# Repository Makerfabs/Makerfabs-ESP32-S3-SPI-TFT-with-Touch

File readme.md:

# Makerfabs ESP32-S3 SPI TFT with Touch

```c++
/*
Version:		V1.4
Author:			Vincent
Create Date:	2022/7/13
Note:
			2022/12/29	V1.4: Change wiki link
			2022/10/10	V1.3: Add Touch Keyboard demo and Back Light demo.
			2022/8/19	V1.2: Add hardware file.
			2022/8/18	V1.1: Add two demo.
			
*/
```

[toc]

# Makerfabs

[Makerfabs home page](https://www.makerfabs.com/)

[Makerfabs Wiki](https://wiki.makerfabs.com/)

# Makerfabs ESP32-S3 SPI TFT with Touch
## Intruduce

Product Link ：[ESP32-S3 SPI TFT with Touch 3.5'' ILI9488](https://www.makerfabs.com/esp32-s3-spi-tft-with-touch-ili9488.html)

Wiki Link : [ESP32-S3 SPI 3.5" TFT with Touch](https://wiki.makerfabs.com/ESP32_S3_SPI_3.5_TFT_with_Touch.html)

The 3.5" 320x480 TFT LCD driver is ILI9488, it uses SPI line for communication with ESP32-S3. You can freely use some of GPIO, to connect the ESP32-S3 display with sensors/ actuators, suitable for IoT applications.

## Feature

- Wi-Fi (2.4 GHz band)
- Bluetooth Low Energy
- Dual high performance Xtensa® 32-bit LX7 CPU cores
- Ultra Low Power co-processor running either RISC-V or FSM core
- Multiple peripherals
- Built-in security hardware
- USB OTG interface
- USB Serial/JTAG Controller
- Arduino Compatible: You can play it with Arduino IDE
- LCD 3.5 inch Amorphous-TFT-LCD (Thin Film Transistor Liquid Crystal Display) for mobile-phone or handy electrical equipment
- LCD Driver: ILI9488(SPI)
- LCD Resolution: 320*480
- FT6236 Series ICs are single-chip capacitive touch panel controller IC with a built-in 16 bit enhanced Micro-controller unit (MCU)
- Power supply: 5V, Type-C USB
- Micro SD card slot on the board
- Dual USB Type-C: one for native USB and one for USB-to-UART
- Board size: 66mm * 85mm

# Code Explain

## Complier Option

- Install board : ESP32 .
- Install library : LovyanGFX library. 
- Use type-c use cable connect USB-TTL to PC.
- Upload codes, select "ESP32-S3 DEV Module" and "UART0"

## Firmware

### S3_9488

A simple test procedure. Touch the black area in the middle of the screen, and the screen starts showing solid colors in turn. Finally, an SD card image is displayed.

## Example

### image_display.ino

The BMP image of the SD card is displayed.

### indoor

[ESP32 Touch_Indoor Environment Expansion](https://www.makerfabs.com/esp32-touch-indoor-environment-expansion.html)

Test air temperature, humidity, and TVOC values with extension plate.

### Touch Keyboard

Added an inherited three custom keyboard keyboard Demo, including text input + key combination, numeric keypad, arrow keys + space.

### Back Light

Periodically adjust the brightness of the backlight

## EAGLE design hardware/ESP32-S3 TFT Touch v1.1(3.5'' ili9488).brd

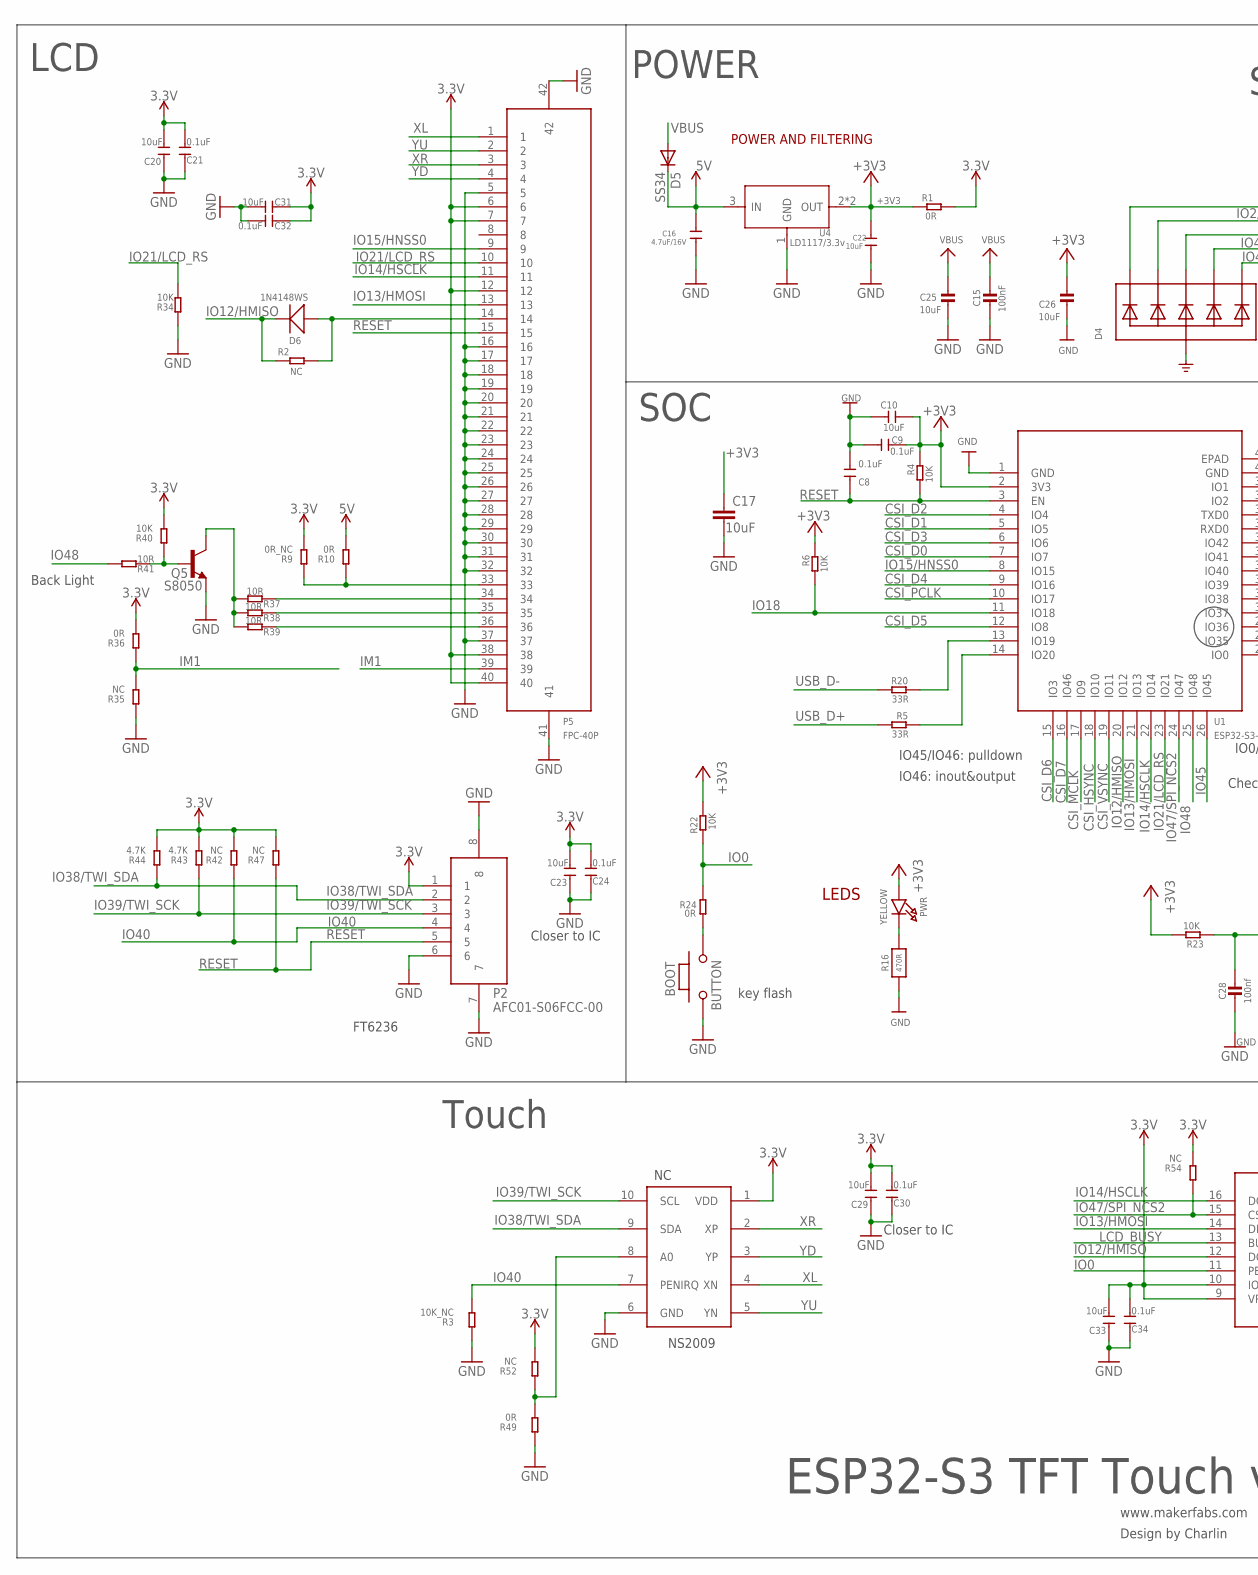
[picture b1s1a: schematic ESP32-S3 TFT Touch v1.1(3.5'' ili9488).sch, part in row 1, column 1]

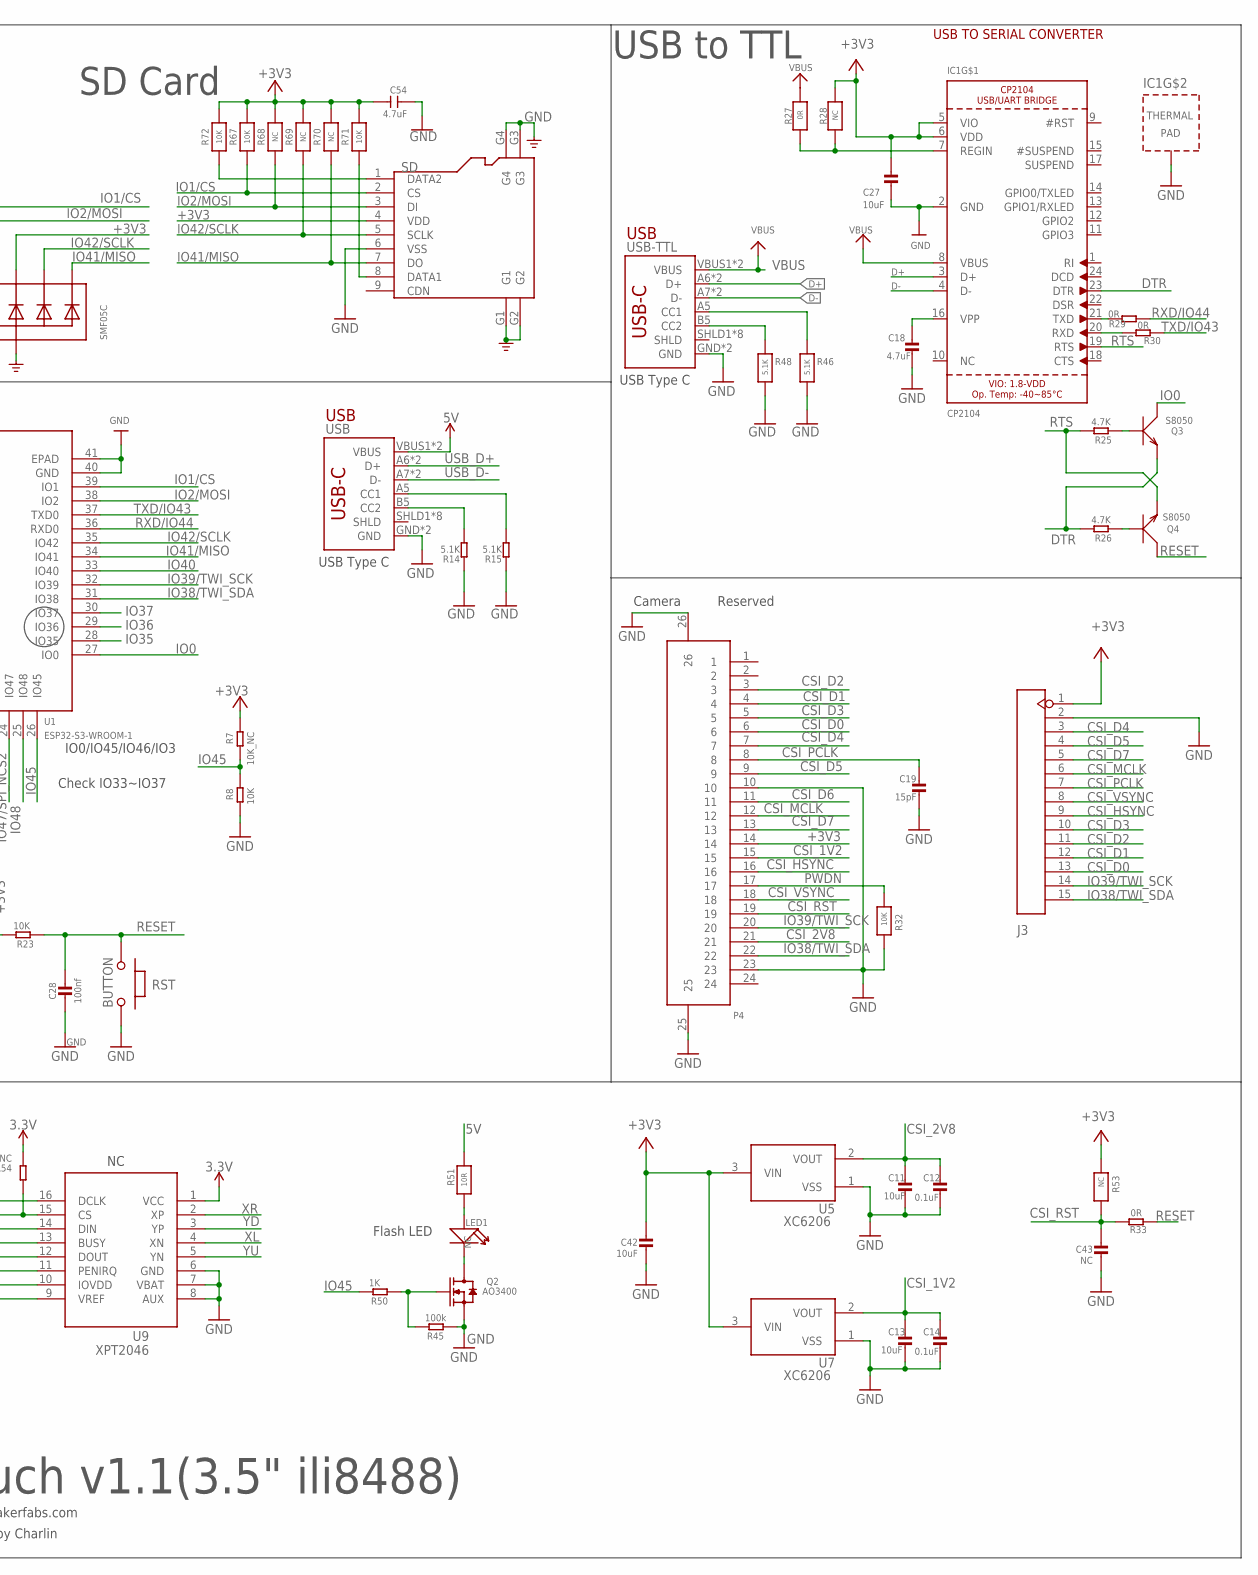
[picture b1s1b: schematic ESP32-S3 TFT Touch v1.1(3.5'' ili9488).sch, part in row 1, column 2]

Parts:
BOOT: BUTTON; 157SW
C8, C9, C21, C24, C30, C32, C34: 0.1uF; DISCRETE_C0603
C10, C20, C23, C29, C31, C33: 10uF; DISCRETE_C0603
C11, C13, C25, C26, C27, C42: 10uF; 0603-NO
C12, C14: 0.1uF; 0603-NO
C15: 100nF; 0603-NO
C16: 4.7uF/16V; 0603
C17: 10uF; C0603
C18: 4.7uF; 0603-NO
C19: 15pF; 0603-NO
C22: 10uF; 0603
C28: 100nf; 0603-NO
C43: NC; 0603-NO
C54: 4.7uF; DISCRETE_C0603
D4: SMF05C; SOT363
D5: SS34; DO-214AC
D6: 1N4148WS; SOD323
IC1: CP2104; QFN24_4MM_SMSC
J3: HEADER-1X15P; SMD15-2.54P8.5H
LED1: NC; DISCRETE_LED-3528
P2: AFC01-S06FCC-00; SMD8-50P-740L535W
P4: FPC-24P; SMD26-50P-1760L450W
P5: FPC-40P; SMD42-50P-2560L490W
PWR: YELLOW; CHIPLED_0805_NOOUTLINE
Q2: AO3400; SOT23@1
Q3, Q4: S8050; SOT23
Q5: S8050; SPARKFUN_SOT23
R1, R24, R29, R30, R33: 0R; R0603
R2: NC; R0603
R3: 10K_NC; DISCRETE_R0603
R4, R6, R8, R22, R23: 10K; R0603
R5, R20: 33R; R0603
R7: 10K_NC; R0603
R9: 0R_NC; DISCRETE_R0603
R10, R36, R49: 0R; DISCRETE_R0603
R14, R15: 5.1K; DISCRETE_R0603
R16: 470R; 0603-NO
R25, R26: 4.7K; R0603
R27: 0R; 0603-NO
R28, R53, R68, R69, R70: NC; 0603-NO
R32, R67, R71, R72: 10K; 0603-NO
R34, R40: 10K; DISCRETE_R0603
R35, R42, R47, R52, R54: NC; DISCRETE_R0603
R37, R38, R39, R41: 10R; DISCRETE_R0603
R43, R44: 4.7K; DISCRETE_R0603
R45: 100k; R0603
R46, R48: 5.1K; 0603-NO
R50: 1K; R0603
R51: 10R; 0603-NO
RST: BUTTON; 157SW
SD: HOLDER-MICROSD-9P; 9P-SMD-W/-RING
U1: ESP32-S3-WROOM-1
U4: LD1117/3.3v; SOT89
U5, U7: XC6206; SOT-23
U8: NS2009; MSOP10
U9: XPT2046; TSSOP16-65P-560L910W
USB: USB_C5; USB-C-16P-5
USB-TTL: USB_C5; USB-C-16P-5

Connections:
3.3V: C20.2, C21.2, C23.2, C24.2, C29.2, C30.2, C31.1, C32.1, C33.2, C34.2, P2.1, P5.6, P5.7, P5.12, P5.38, P5.40, R1.2, R9.2, R36.2, R40.2, R42.2, R43.2, R44.2, R47.2, R52.2, R54.2, U8.1 (VDD), U9.1 (VCC), U9.9 (VREF), U9.10 (IOVDD)
5V: C16.1, D5.C, R10.2, R51.1, U4.3 (IN), USB.VBUS1 (VBUS), USB.VBUS2 (VBUS)
+3V3: C9.1, C10.1, C17.1, C22.1, C26.1, C27.1, C42.1, C54.2, D4.4 (C3), IC1.5 (VIO), IC1.6 (VDD), J3.1, P4.14, PWR.A, R1.1, R4.2, R6.2, R7.2, R22.2, R23.2, R28.1, R53.1, R67.2, R68.2, R69.2, R70.2, R71.2, R72.2, SD.4 (VDD), U1.2 (3V3), U4.2 (OUT), U4.4 (OUT), U5.3 (VIN), U7.3 (VIN)
CSI_1V2: C13.1, C14.1, P4.15, U7.2 (VOUT)
CSI_2V8: C11.1, C12.1, P4.21, U5.2 (VOUT)
CSI_D0: J3.13, P4.6, U1.7 (IO7)
CSI_D1: J3.12, P4.4, U1.5 (IO5)
CSI_D2: J3.11, P4.3, U1.4 (IO4)
CSI_D3: J3.10, P4.5, U1.6 (IO6)
CSI_D4: J3.3, P4.7, U1.9 (IO16)
CSI_D5: J3.4, P4.9, U1.12 (IO8)
CSI_D6: P4.11, U1.15 (IO3)
CSI_D7: J3.5, P4.13, U1.16 (IO46)
CSI_HSYNC: J3.9, P4.16, U1.18 (IO10)
CSI_MCLK: J3.6, P4.12, U1.17 (IO9)
CSI_PCLK: C19.1, J3.7, P4.8, U1.10 (IO17)
CSI_RST: C43.1, P4.19, R33.2, R53.2
CSI_VSYNC: J3.8, P4.18, U1.19 (IO11)
D+: IC1.3 (D+), USB-TTL.A6 (D+), USB-TTL.B6 (D+)
D-: IC1.4 (D-), USB-TTL.A7 (D-), USB-TTL.B7 (D-)
DTR: IC1.23 (DTR), Q3.2 (E), R26.2
GND: BOOT.1, C8.2, C9.2, C10.2, C11.2, C12.2, C13.2, C14.2, C15.2, C16.2, C17.2, C18.2, C19.2, C20.1, C21.1, C22.2, C23.1, C24.1, C25.2, C26.2, C27.2, C28.2, C29.1, C30.1, C31.2, C32.2, C33.1, C34.1, C42.2, C43.2, C54.1, D4.2 (A), IC1.2 (GND), IC1.THERM (TP), J3.2, P2.6, P2.7, P2.8, P4.10, P4.23, P4.25, P4.26, P5.5, P5.16, P5.17, P5.18, P5.19, P5.20, P5.21, P5.22, P5.23, P5.24, P5.25, P5.26, P5.27, P5.28, P5.29, P5.30, P5.31, P5.32, P5.37, P5.41, P5.42, Q2.2 (S), Q5.2 (E), R3.1, R8.1, R14.1, R15.1, R16.1, R32.2, R34.1, R35.1, R45.1, R46.2, R48.2, R49.1, RST.1, SD.6 (VSS), SD.G1, SD.G2, SD.G3, SD.G4, U1.1 (GND), U1.40 (GND), U1.41 (EPAD), U4.1 (GND), U5.1 (VSS), U7.1 (VSS), U8.6 (GND), U9.6 (GND), U9.7 (VBAT), U9.8 (AUX), USB.GND, USB.GND2 (GND), USB-TTL.GND, USB-TTL.GND2 (GND)
IM1: P5.39, R35.2, R36.1
IO0: Q3.3 (C), R22.1, R24.2, U1.27 (IO0), U9.11 (PENIRQ)
IO1/CS: D4.1 (C1), R67.1, SD.2 (CS), U1.39 (IO1)
IO2/MOSI: D4.3 (C2), R68.1, SD.3 (DI), U1.38 (IO2)
IO12/HMISO: D6.-, R2.1, U1.20 (IO12), U9.12 (DOUT)
IO13/HMOSI: P5.13, U1.21 (IO13), U9.14 (DIN)
IO14/HSCLK: P5.11, U1.22 (IO14), U9.16 (DCLK)
IO15/HNSS0: P5.9, U1.8 (IO15)
IO18: R6.1, U1.11 (IO18)
IO21/LCD_RS: P5.10, R34.2, U1.23 (IO21)
IO35: U1.28 (IO35)
IO36: U1.29 (IO36)
IO37: U1.30 (IO37)
IO38/TWI_SDA: J3.15, P2.2, P4.22, R44.1, U1.31 (IO38), U8.9 (SDA)
IO39/TWI_SCK: J3.14, P2.3, P4.20, R43.1, U1.32 (IO39), U8.10 (SCL)
IO40: P2.4, R3.2, R42.1, U1.33 (IO40), U8.7 (PENIRQ)
IO41/MISO: D4.6 (C5), R70.1, SD.7 (DO), U1.34 (IO41)
IO42/SCLK: D4.5 (C4), R69.1, SD.5 (SCLK), U1.35 (IO42)
IO45: R7.1, R8.2, R50.2, U1.26 (IO45)
IO47/SPI_NCS2: R54.1, U1.24 (IO47), U9.15 (CS)
IO48: R41.2, U1.25 (IO48)
LCD_BUSY: U9.13 (BUSY)
unnamed: C18.1, IC1.16 (VPP)
unnamed: Q4.1 (B), R26.1
unnamed: Q3.1 (B), R25.1
unnamed: D6.+, P5.14, R2.2
unnamed: Q2.1 (G), R45.2, R50.1
unnamed: BOOT.2, R24.1
unnamed: PWR.C, R16.2
unnamed: LED1.1 (+), R51.2
unnamed: LED1.2 (-), Q2.3 (D)
unnamed: R46.1, USB-TTL.A5 (CC1)
unnamed: R48.1, USB-TTL.B5 (CC2)
unnamed: IC1.7 (REGIN), R27.2, R28.2
unnamed: R15.2, USB.A5 (CC1)
unnamed: R20.2, U1.13 (IO19)
unnamed: R5.2, U1.14 (IO20)
unnamed: R14.2, USB.B5 (CC2)
unnamed: IC1.21 (TXD), R29.2
unnamed: IC1.20 (RXD), R30.2
unnamed: P5.34, R37.1
unnamed: P5.35, R38.1
unnamed: P5.36, R39.1
unnamed: Q5.1 (B), R40.1, R41.1
unnamed: Q5.3 (C), R37.2, R38.2, R39.2
unnamed: R49.2, R52.1, U8.8 (A0)
unnamed: P5.33, R9.1, R10.1
unnamed: R72.1, SD.1 (DATA2)
unnamed: R71.1, SD.8 (DATA1)
PWDN: P4.17, R32.1
RESET: C8.1, C28.1, P2.5, P5.15, Q4.3 (C), R4.1, R23.1, R33.1, R47.1, RST.2, U1.3 (EN)
RTS: IC1.19 (RTS), Q4.2 (E), R25.2
RXD/IO44: R29.1, U1.36 (RXD0)
TXD/IO43: R30.1, U1.37 (TXD0)
USB_D+: R5.1, USB.A6 (D+), USB.B6 (D+)
USB_D-: R20.1, USB.A7 (D-), USB.B7 (D-)
VBUS: C15.1, C25.1, D5.A, IC1.8 (VBUS), R27.1, USB-TTL.VBUS1 (VBUS), USB-TTL.VBUS2 (VBUS)
XL: P5.1, U8.4 (XN), U9.4 (XN)
XR: P5.3, U8.2 (XP), U9.2 (XP)
YD: P5.4, U8.3 (YP), U9.3 (YP)
YU: P5.2, U8.5 (YN), U9.5 (YN)

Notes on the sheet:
www.makerfabs.com
Design by Charlin
USB
LEDS
POWER AND FILTERING
USB TO SERIAL CONVERTER
key flash
ESP32-S3 TFT Touch v1.1(3.5" ili8488)
POWER
USB to TTL
USB Type C
SD Card
Flash LED
Camera
NS2009
FT6236
Closer to IC
Back Light
IO45/IO46: pulldown
IO46: inout&output
IO0/IO45/IO46/IO3
Check IO33~IO37
LCD
SOC
Touch
Reserved

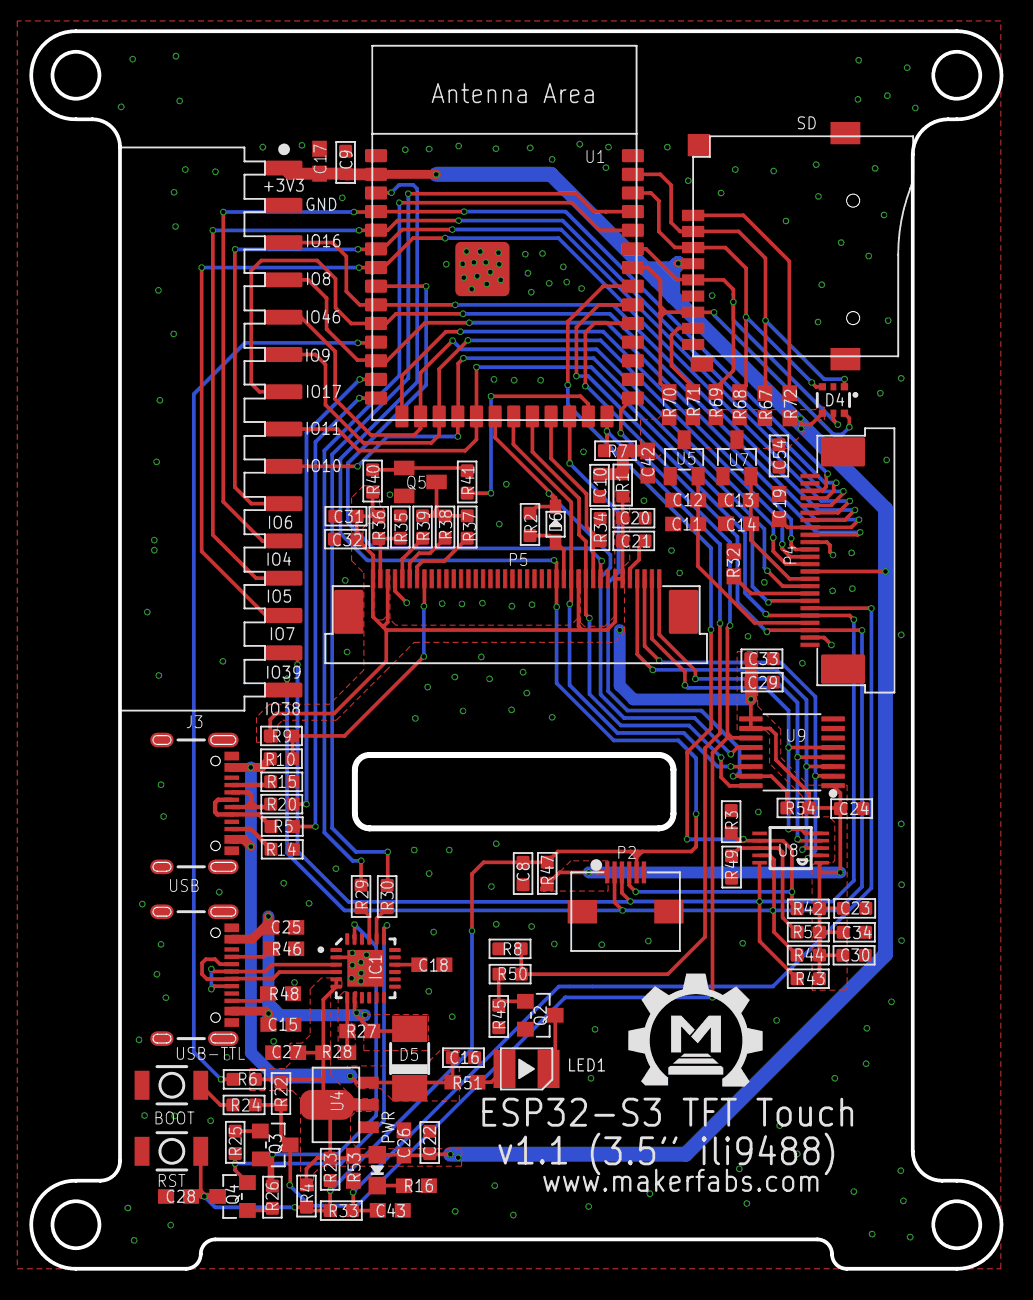
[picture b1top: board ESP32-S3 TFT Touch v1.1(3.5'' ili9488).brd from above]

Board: 2 copper layers, 66.1 x 84.3 mm, 108 parts (0 on the bottom side), 79 nets.

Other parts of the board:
U$1: MAKERFABS_0.3

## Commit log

2022-07-13 Create
2022-08-18 Add two demo
2022-08-19 V1.2
2022-10-10 V1.3
2024-09-30 add demo
2024-12-25 Create keydo_touch
    MS Teams quick access buttons
2024-12-25 Add files via upload
    Control MS Teams :
    Mute Microphone, Accept calls, end calls, toggle video and mute speakers.
2025-04-01 Add Arduino GFX Library demo
2025-11-20 add esp-idf examples
2026-01-04 update idf example
2026-01-04 delect example/esp-idf

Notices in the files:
parts and their libraries:
microbuilder: This work is placed in the public domain, and may be freely used for commercial and non-commercial work with the following conditions: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
SparkFun-PowerSymbols: Licensing: Creative Commons ShareAlike 4.0 International - https://creativecommons.org/licenses/by-sa/4.0
